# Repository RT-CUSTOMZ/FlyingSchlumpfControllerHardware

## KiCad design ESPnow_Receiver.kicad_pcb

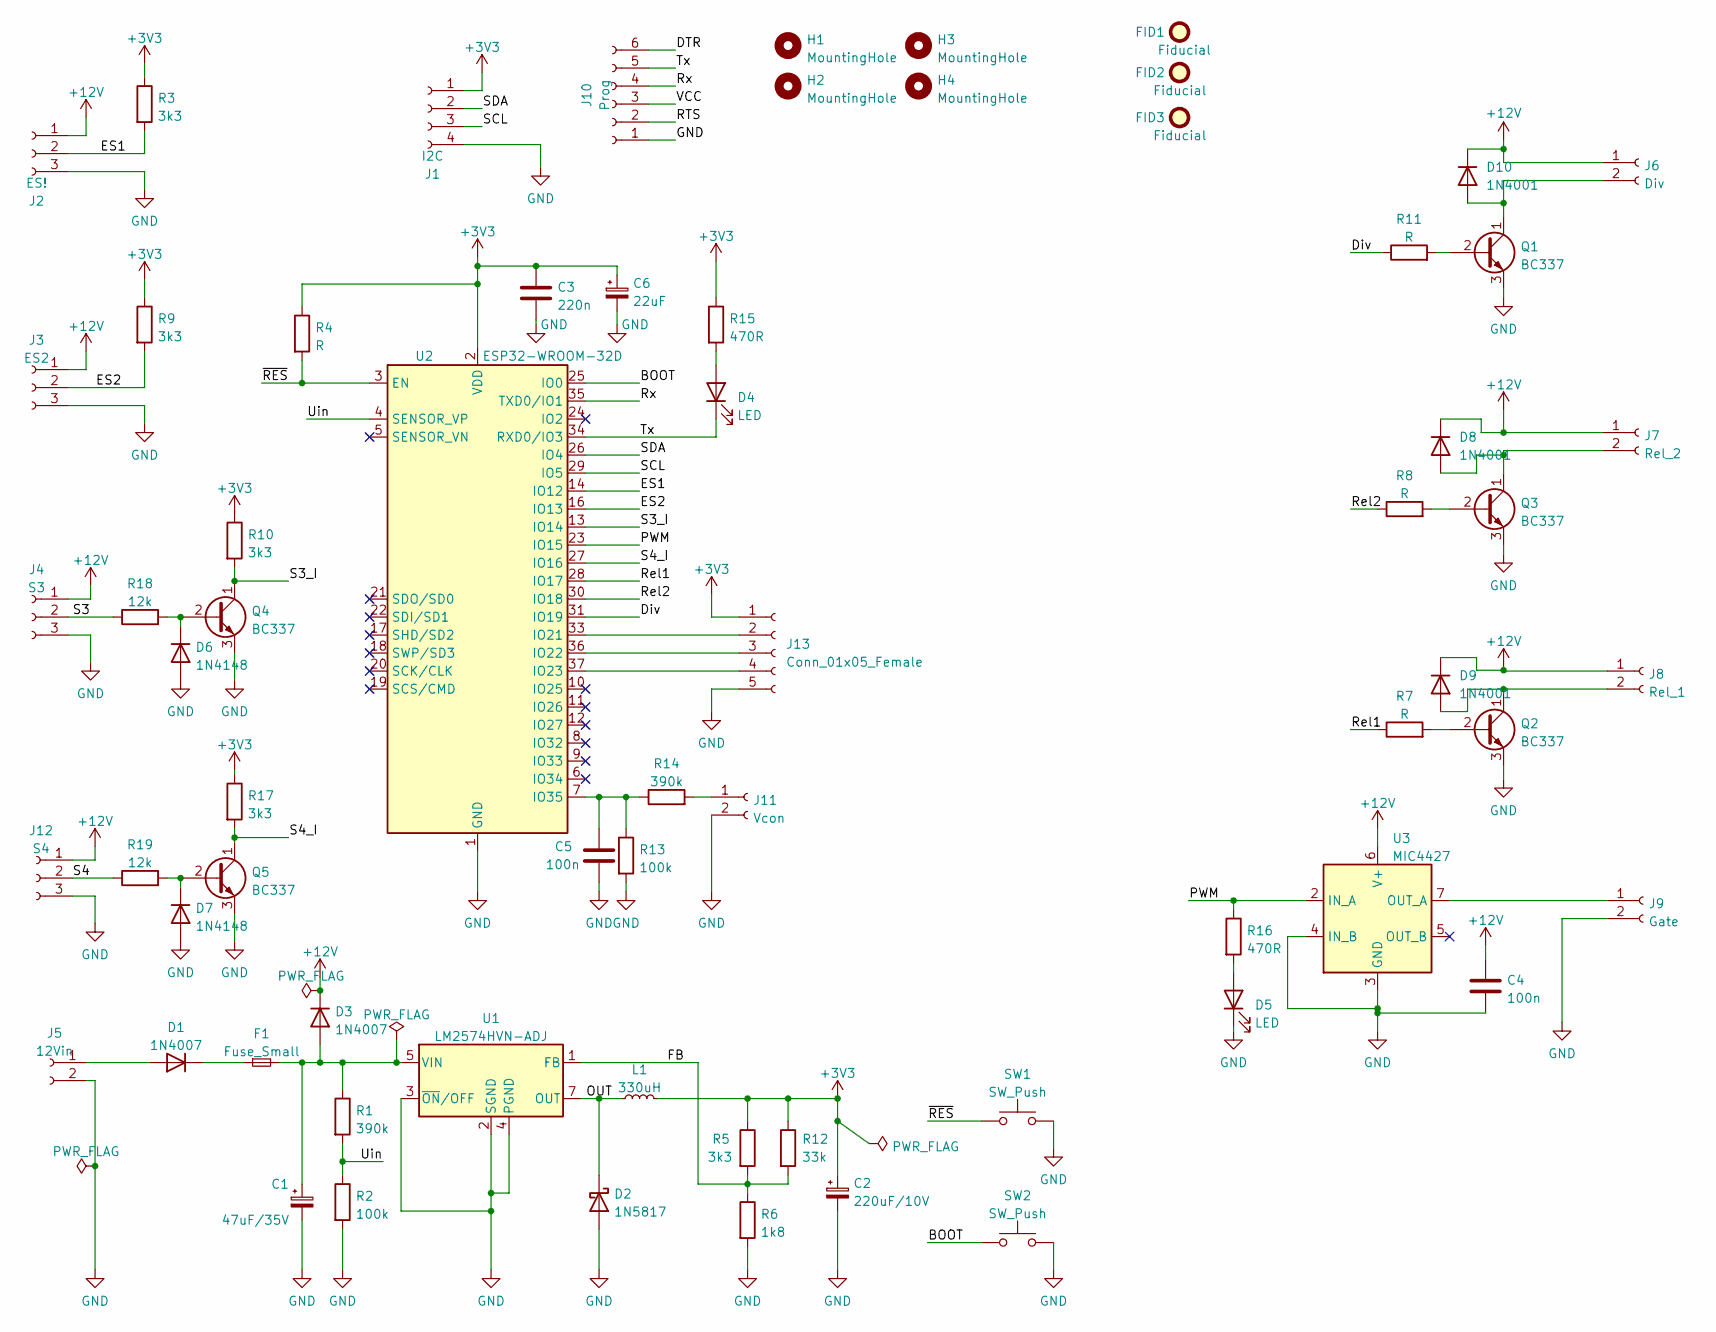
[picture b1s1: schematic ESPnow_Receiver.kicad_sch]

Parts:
C1: 47uF/35V; CP_Radial_D10.0mm_P3.80mm
C2: 220uF/10V; CP_Radial_D10.0mm_P3.50mm
C3: 220n; C_Disc_D5.0mm_W2.5mm_P5.00mm
C4, C5: 100n; C_Disc_D5.0mm_W2.5mm_P5.00mm
C6: 22uF; CP_Radial_D10.0mm_P3.50mm
D1, D3: 1N4007; D_DO-41_SOD81_P10.16mm_Horizontal
D2: 1N5817; D_DO-41_SOD81_P10.16mm_Horizontal
D4, D5: LED; LED_D3.0mm
D6, D7: 1N4148; D_DO-35_SOD27_P7.62mm_Horizontal
D8, D9, D10: 1N4001; D_DO-41_SOD81_P10.16mm_Horizontal
F1: Fuse_Small; Fuseholder_Littelfuse_100_series_5x20mm
FID1, FID2, FID3: Fiducial; Fiducial_1.5mm_Mask3mm
H1, H2, H3, H4: MountingHole; MountingHole_3.2mm_M3
J1: I2C; Molex_KK-254_AE-6410-04A_1x04_P2.54mm_Vertical
J2: ES!; PhoenixContact_MSTBA_2,5_3-G-5,08_1x03_P5.08mm_Horizontal
J3: ES2; PhoenixContact_MSTBA_2,5_3-G-5,08_1x03_P5.08mm_Horizontal
J4: S3; PhoenixContact_MSTBA_2,5_3-G-5,08_1x03_P5.08mm_Horizontal
J5: 12Vin; PhoenixContact_MSTBA_2,5_2-G_1x02_P5.00mm_Horizontal
J6: Div; PhoenixContact_MSTBA_2,5_2-G_1x02_P5.00mm_Horizontal
J7: Rel_2; PhoenixContact_MSTBA_2,5_2-G_1x02_P5.00mm_Horizontal
J8: Rel_1; PhoenixContact_MSTBA_2,5_2-G_1x02_P5.00mm_Horizontal
J9: Gate; PhoenixContact_MSTBA_2,5_2-G_1x02_P5.00mm_Horizontal
J10: Prog; PinSocket_1x06_P2.54mm_Vertical
J11: Vcon; Molex_KK-254_AE-6410-02A_1x02_P2.54mm_Vertical
J12: S4; PhoenixContact_MSTBA_2,5_3-G-5,08_1x03_P5.08mm_Horizontal
J13: Conn_01x05_Female; PinSocket_1x05_P2.54mm_Vertical
L1: 330uH; L_Radial_D10.0mm_P5.00mm_Neosid_SD12_style3
Q1, Q2, Q3, Q4, Q5: BC337; TO-92_HandSolder
R1, R14: 390k; R_Axial_DIN0207_L6.3mm_D2.5mm_P10.16mm_Horizontal
R2, R13: 100k; R_Axial_DIN0207_L6.3mm_D2.5mm_P10.16mm_Horizontal
R3, R5, R9, R10, R17: 3k3; R_Axial_DIN0207_L6.3mm_D2.5mm_P10.16mm_Horizontal
R4, R7, R8, R11: R; R_Axial_DIN0207_L6.3mm_D2.5mm_P10.16mm_Horizontal
R6: 1k8; R_Axial_DIN0207_L6.3mm_D2.5mm_P10.16mm_Horizontal
R12: 33k; R_Axial_DIN0207_L6.3mm_D2.5mm_P10.16mm_Horizontal
R15, R16: 470R; R_Axial_DIN0207_L6.3mm_D2.5mm_P10.16mm_Horizontal
R18, R19: 12k; R_Axial_DIN0207_L6.3mm_D2.5mm_P10.16mm_Horizontal
SW1, SW2: SW_Push; Push_E-Switch_KS01Q01
U1: LM2574HVN-ADJ; DIP-8_W7.62mm
U2: ESP32-WROOM-32D; ESP32-WROOM-32
U3: MIC4427; DIP-8_W7.62mm

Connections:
+3V3: C2.1, C3.1, C6.1, J1.1, J13.1, L1.2, R3.1, R4.1, R5.1, R9.1, R10.1, R12.1, R15.1, R17.1, U2.2 (VDD)
+12V: C4.1, D3.1 (K), D8.1 (K), D9.1 (K), D10.1 (K), J2.1, J3.1, J4.1, J6.1, J7.1, J8.1, J12.1, U3.6 (V+)
/BOOT: SW2.1, U2.25 (IO0)
/DTR: J10.6
/Div: R11.1, U2.31 (IO19)
/ES1: J2.2, R3.2, U2.14 (IO12)
/ES2: J3.2, R9.2, U2.16 (IO13)
/FB: R5.2, R6.1, R12.2, U1.1 (FB)
/OUT: D2.1 (K), L1.1, U1.7 (OUT)
/PWM: R16.1, U2.23 (IO15), U3.2 (IN_A)
/RTS: J10.2
/Rel1: R7.1, U2.28 (IO17)
/Rel2: R8.1, U2.30 (IO18)
/Rx: J10.4, U2.35 (TXD0/IO1)
/S3: J4.2, R18.1
/S3_I: Q4.1 (C), R10.2, U2.13 (IO14)
/S4: J12.2, R19.1
/S4_I: Q5.1 (C), R17.2, U2.27 (IO16)
/SCL: J1.3, U2.29 (IO5)
/SDA: J1.2, U2.26 (IO4)
/Tx: D4.1 (K), J10.5, U2.34 (RXD0/IO3)
/Uin: R1.2, R2.1, U2.4 (SENSOR_VP)
/VCC: J10.3
/~RES: R4.2, SW1.1, U2.3 (EN)
GND: C1.2, C2.2, C3.2, C4.2, C5.2, C6.2, D2.2 (A), D5.1 (K), D6.2 (A), D7.2 (A), J1.4, J2.3, J3.3, J4.3, J5.2, J9.2, J10.1, J11.2, J12.3, J13.5, Q1.3 (E), Q2.3 (E), Q3.3 (E), Q4.3 (E), Q5.3 (E), R2.2, R6.2, R13.2, SW1.2, SW2.2, U1.2 (SGND), U1.3 (~ON/OFF), U1.4 (PGND), U2.1 (GND), U2.15 (GND), U2.38 (GND), U2.39 (GND), U3.3 (GND), U3.4 (IN_B)
unnamed: C1.1, D3.2 (A), F1.2, R1.1, U1.5 (VIN)
unnamed: C5.1, R13.1, R14.1, U2.7 (IO35)
unnamed: D1.1 (K), F1.1
unnamed: D1.2 (A), J5.1
unnamed: D4.2 (A), R15.2
unnamed: D5.2 (A), R16.2
unnamed: D6.1 (K), Q4.2 (B), R18.2
unnamed: D7.1 (K), Q5.2 (B), R19.2
unnamed: D8.2 (A), J7.2, Q3.1 (C)
unnamed: D9.2 (A), J8.2, Q2.1 (C)
unnamed: D10.2 (A), J6.2, Q1.1 (C)
unnamed: J9.1, U3.7 (OUT_A)
unnamed: J11.1, R14.2
unnamed: J13.2, U2.33 (IO21)
unnamed: J13.3, U2.36 (IO22)
unnamed: J13.4, U2.37 (IO23)
unnamed: Q1.2 (B), R11.2
unnamed: Q2.2 (B), R7.2
unnamed: Q3.2 (B), R8.2

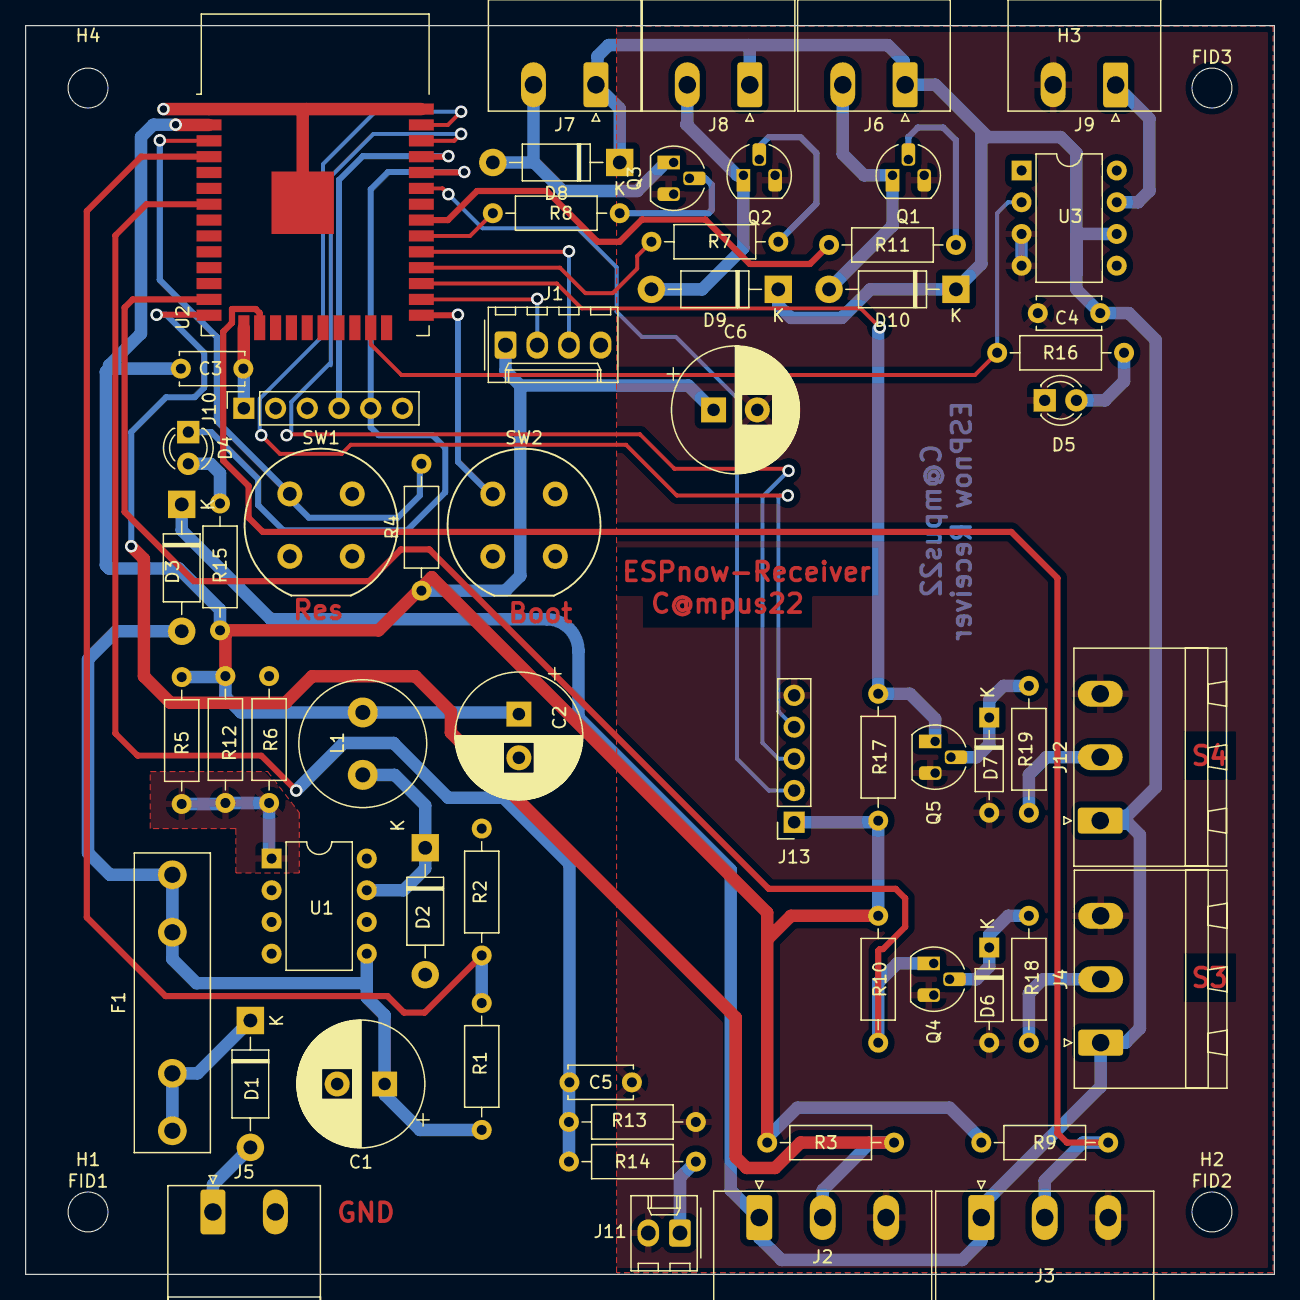
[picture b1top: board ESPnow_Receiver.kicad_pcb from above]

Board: 2 copper layers, 100.0 x 100.0 mm, 67 parts (0 on the bottom side), 41 nets.

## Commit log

2022-08-11 add pdf of Schematic
2022-10-14 Ci (#1)
    Add ci to create InteractiveHtmlBom
2022-10-15 add creation of Schematics PDF export to ci
